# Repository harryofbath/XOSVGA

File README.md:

# Xbox Open Source Video Project - VGA

XOSVP is an open-source alternative to the Microsoft HD AV Pack. The XOSVP strives to produce the absolute best analog video quality out of your original Xbox.

The VGA derivative you see here is an attempt to allow VGA connections between your modded Xbox and a VGA display. It will utilize a compatible pin-out to the original XOSVP-AVIP cable, with the addition of sync and a jumper. This will allow you to use one cable for either XOSVP or XOSVGA. Likewise, the board size will remain the same (hopefully), allowing the pre-existing case design to only require minor modification to allow for the additional DB-15 connector.
Currently, this design has not been tested, or even built, so do not expect it to work by any means. 

## Features
- Highest possible quality analog VGA video out
    - (tbd) Impedance matched board traces and cabling from original Xbox
    - High quality video filter + amplifier, [THS7316](https://www.ti.com/lit/ds/symlink/ths7316.pdf)
        - Low pass filter removes high-frequency noise and aberrations from the source signal without harming video frequencies
        - Reconstructs + Amplifies original signal to ensure matching with the VESA Standards (to check)
        - Reduces DAC Imaging effects on the video receiver
- Optical Audio/SPDIF
    - Best possible audio quality from the original Xbox
    - Support Stereo -> 5.1 Surround Sound
    - Cheap, high-quality optical DAC's easy to source on Amazon/Ebay for those without stereo systems

## More Details
[Check out the in-depth blog post on the original XOSVP detailing its construction, evolution, and comparison images.](https://blog.dtho.mp/2018/12/15/xosvp-intro/)

## Designs (original, to be updated)
- [**Schematics**](/xosvp.pdf)
- [**PCB**](/pcb.png)
- [**BOM**](/bom.csv)
- [**Enclosure**](/enclosure.obj)

All designs were produced with KiCAD 5. This includes all schematic sources, designed footprints, and PCB layout. VGA designs created in KiCAD 8.

## Enclosure (to be modified to fit 2nd DB-15 Connector)

Also within this repo is a 3D printable enclosure for the XOSVP. It is designed for friction fit so please ensure your 3D printer is calibrated properly before printing. All files were exported with Millimeter scale.

The enclosure was designed with Tinkercad, and you can view this design [HERE](https://www.tinkercad.com/things/6Rlx4JstT6S-xosvp-enclosure-v3).

## License
I want high-quality analog video from the original Xbox to be available to everyone, which is why I open sourced this project. Everything within this repo is covered by [CERN Open Hardware License v1.2](/LICENSE).

The VGA project has equal aims, and of course is covered by the same license.

## Contributing
If you have any suggested changes/improvements, please feel free to create an issue or a PR. They will be happily accepted!

I, the VGA designer, have limited experience with PCB design, so any input is greatly appreciated.

# Build Instructions
To Be Revised

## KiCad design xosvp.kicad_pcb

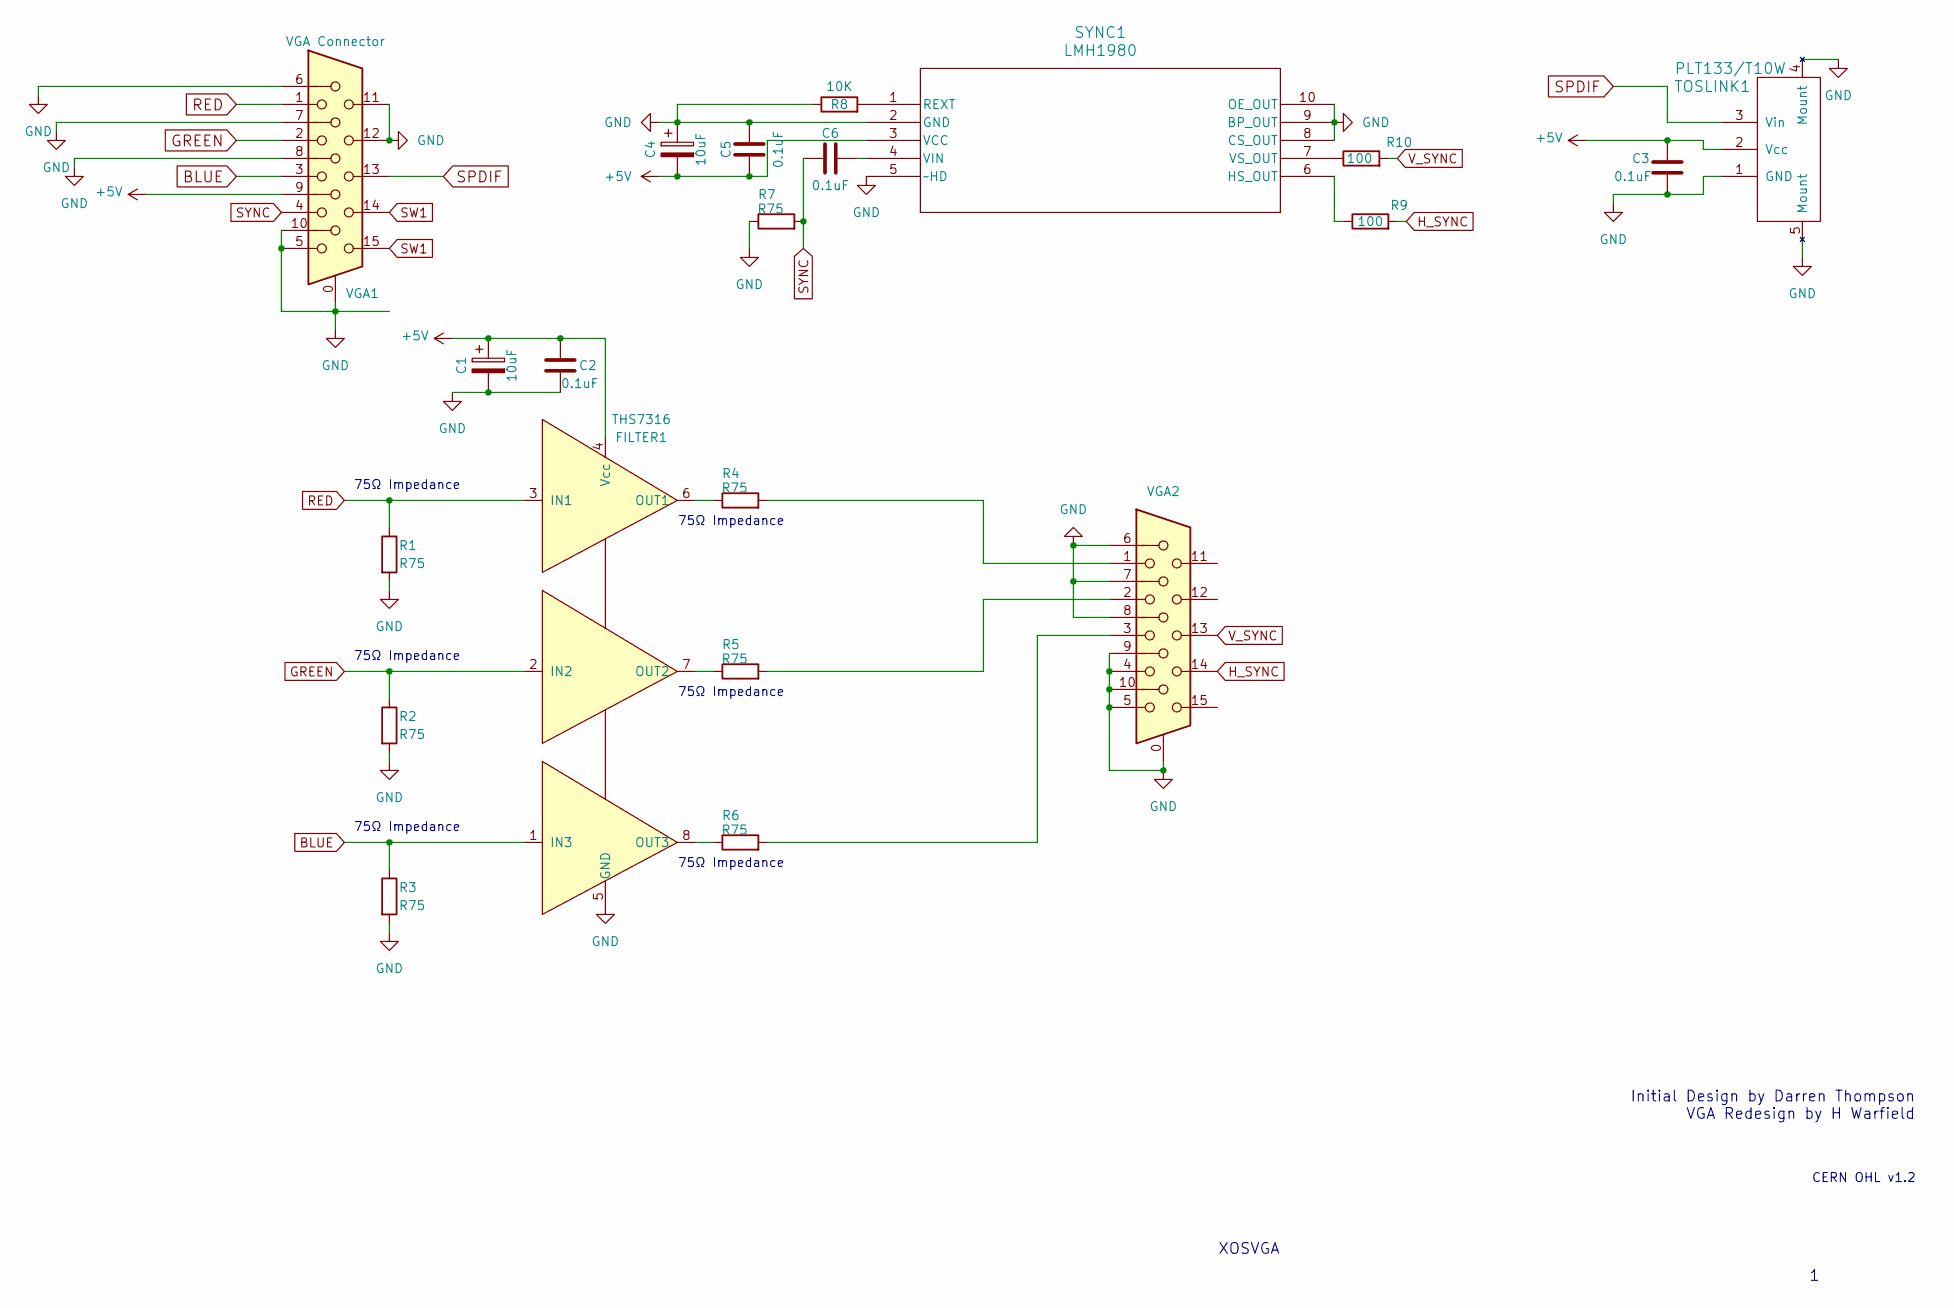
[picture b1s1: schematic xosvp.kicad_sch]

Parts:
C1, C4: 10uF; CP_Elec_4x5.8
C2, C3, C5, C6: 0.1uF; C_0805_2012Metric
FILTER1: THS7316
R1, R2, R3, R4, R5, R6, R7: R75; R_0805_2012Metric
R8: 10K; R_0805_2012Metric
R9, R10: 100; R_0805_2012Metric
SYNC1: LMH1980
TOSLINK1: PLT133/T10W; PLT133
VGA1: VGA Connector; AHDF15A
VGA2: DB15_Female_HighDensity_MountingHoles; AHDF15A

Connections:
+5V: C1.1, C2.1, C3.1, C4.2, C5.1, FILTER1.4 (Vcc), SYNC1.3 (VCC), TOSLINK1.2 (Vcc), VGA1.9
BLUE: FILTER1.1 (IN3), R3.1, VGA1.3
GND: C1.2, C2.2, C3.2, C4.1, C5.2, FILTER1.5 (GND), R1.2, R2.2, R3.2, R7.1, R8.1, SYNC1.2 (GND), SYNC1.5 (~HD), SYNC1.8 (CS_OUT), SYNC1.9 (BP_OUT), SYNC1.10 (OE_OUT), TOSLINK1.1 (GND), TOSLINK1.4 (Mount), TOSLINK1.5 (Mount), VGA1.0, VGA1.5, VGA1.6, VGA1.7, VGA1.8, VGA1.10, VGA1.11, VGA1.12, VGA2.0, VGA2.4, VGA2.5, VGA2.6, VGA2.7, VGA2.8, VGA2.9, VGA2.10
GREEN: FILTER1.2 (IN2), R2.1, VGA1.2
H_SYNC: R9.2, VGA2.14
unnamed: FILTER1.6 (OUT1), R4.1
unnamed: FILTER1.7 (OUT2), R5.1
unnamed: FILTER1.8 (OUT3), R6.1
unnamed: R4.2, VGA2.1
unnamed: R5.2, VGA2.2
unnamed: R6.2, VGA2.3
unnamed: R9.1, SYNC1.6 (HS_OUT)
unnamed: R8.2, SYNC1.1 (REXT)
unnamed: C6.2, SYNC1.4 (VIN)
unnamed: R10.1, SYNC1.7 (VS_OUT)
RED: FILTER1.3 (IN1), R1.1, VGA1.1
SPDIF: TOSLINK1.3 (Vin), VGA1.13
SW1: VGA1.14, VGA1.15
SYNC: C6.1, R7.2, VGA1.4
V_SYNC: R10.2, VGA2.13

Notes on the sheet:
75Ω Impedance
XOSVGA
Initial Design by Darren Thompson VGA Redesign by H Warfield
CERN OHL v1.2

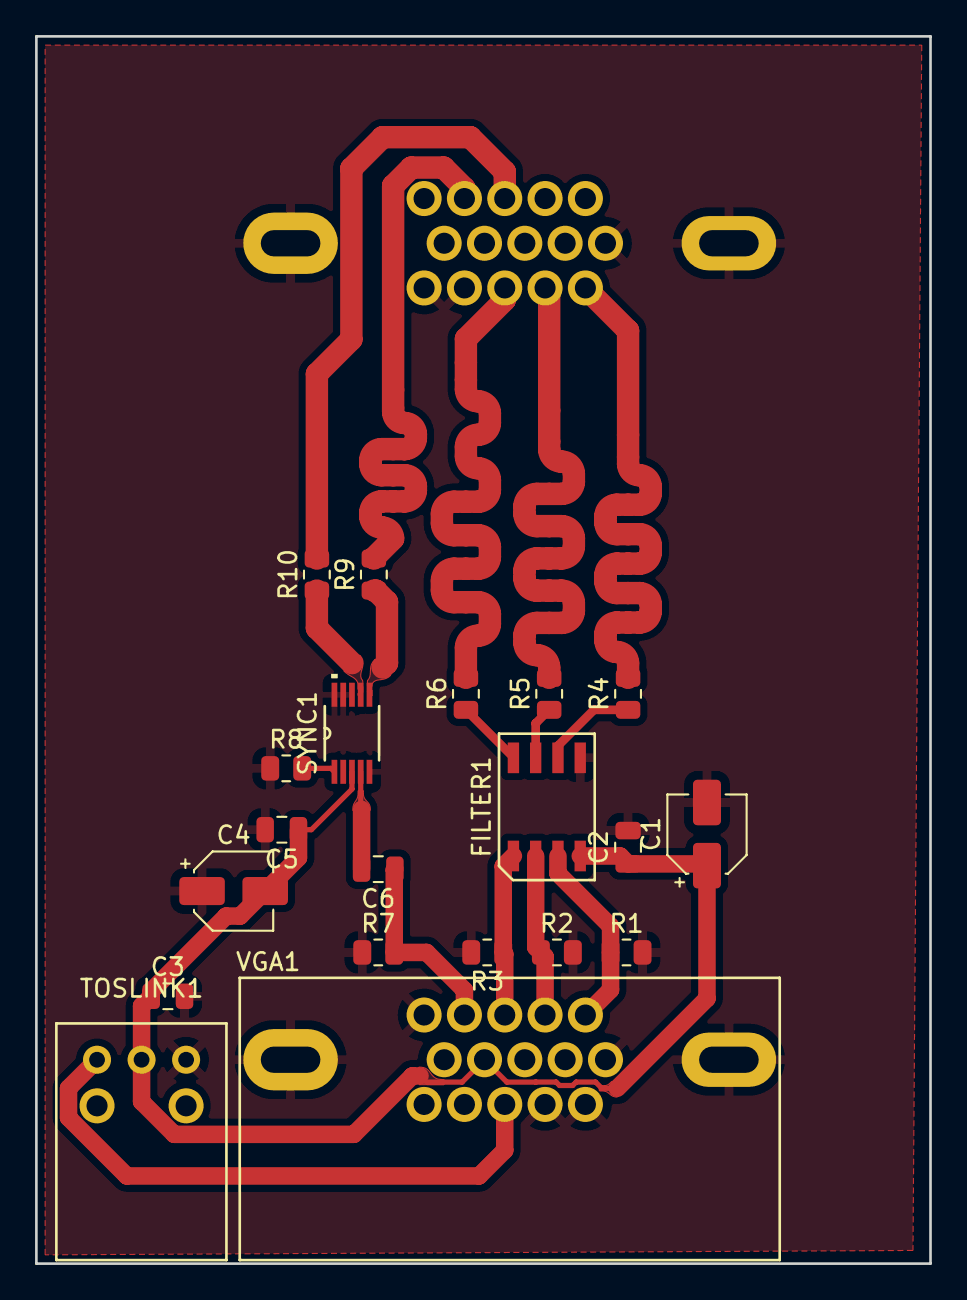
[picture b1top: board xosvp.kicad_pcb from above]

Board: 2 copper layers, 51.0 x 70.0 mm, 21 parts (1 on the bottom side), 20 nets.

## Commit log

2024-10-03 Initial Commit. Major redesign, yet to be finished.
2024-10-03 Delete xosvp-backups directory
    Didn't mean to include this. Oops.
2024-10-04 Have redesigned the pcb again, realizing that the VGA connector must be flipped to prevent crossing the color signals. Have also extended the board to facilitate proper impedance matching, which was 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
